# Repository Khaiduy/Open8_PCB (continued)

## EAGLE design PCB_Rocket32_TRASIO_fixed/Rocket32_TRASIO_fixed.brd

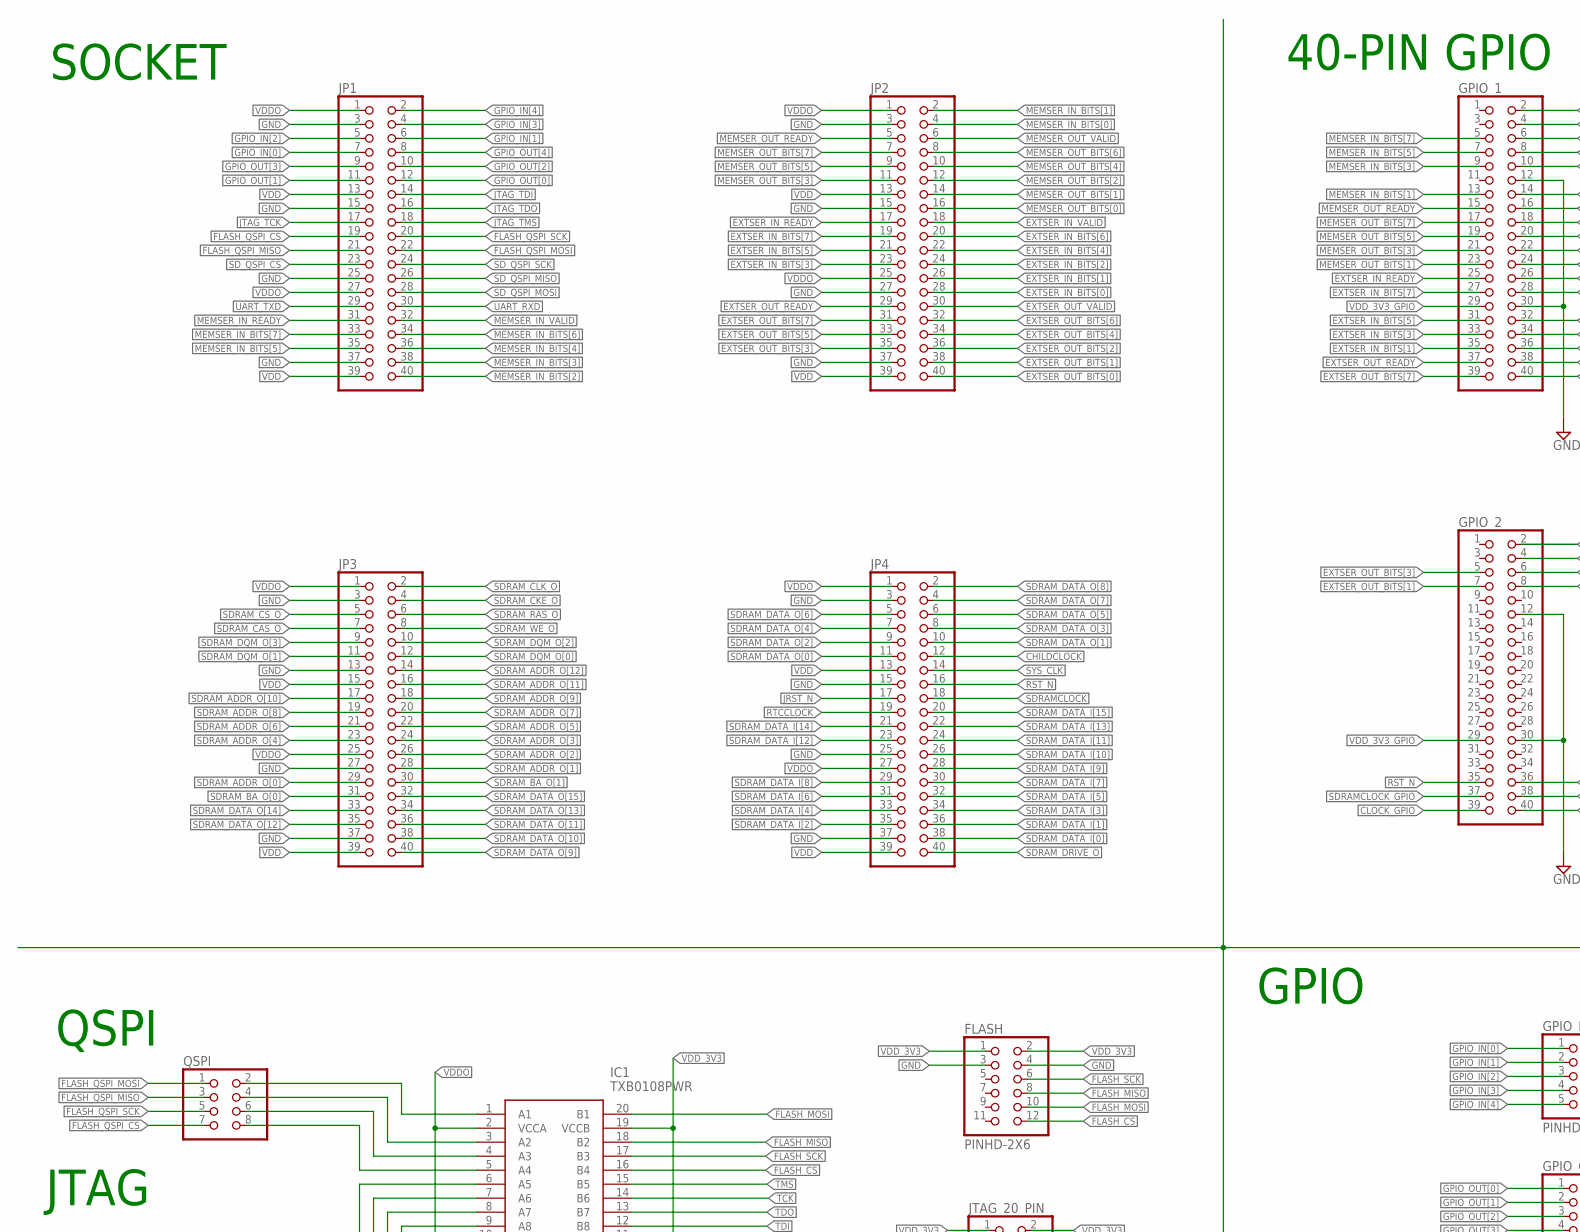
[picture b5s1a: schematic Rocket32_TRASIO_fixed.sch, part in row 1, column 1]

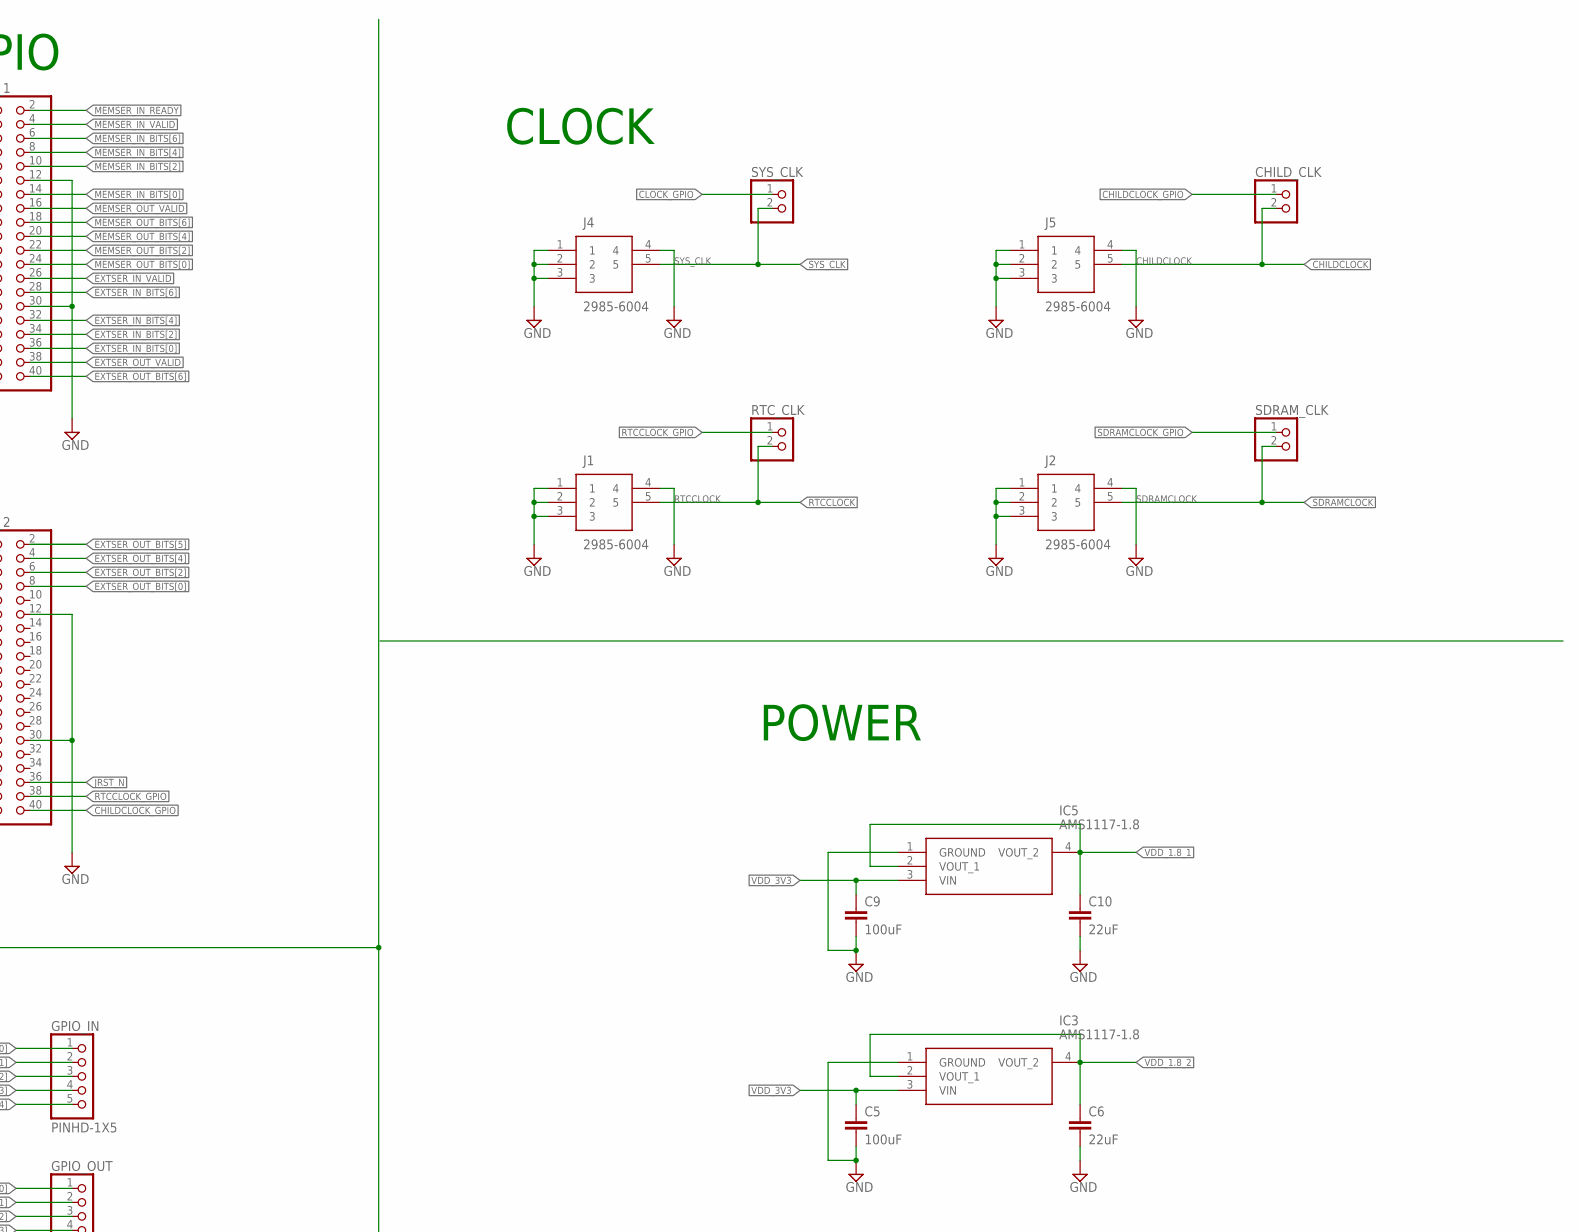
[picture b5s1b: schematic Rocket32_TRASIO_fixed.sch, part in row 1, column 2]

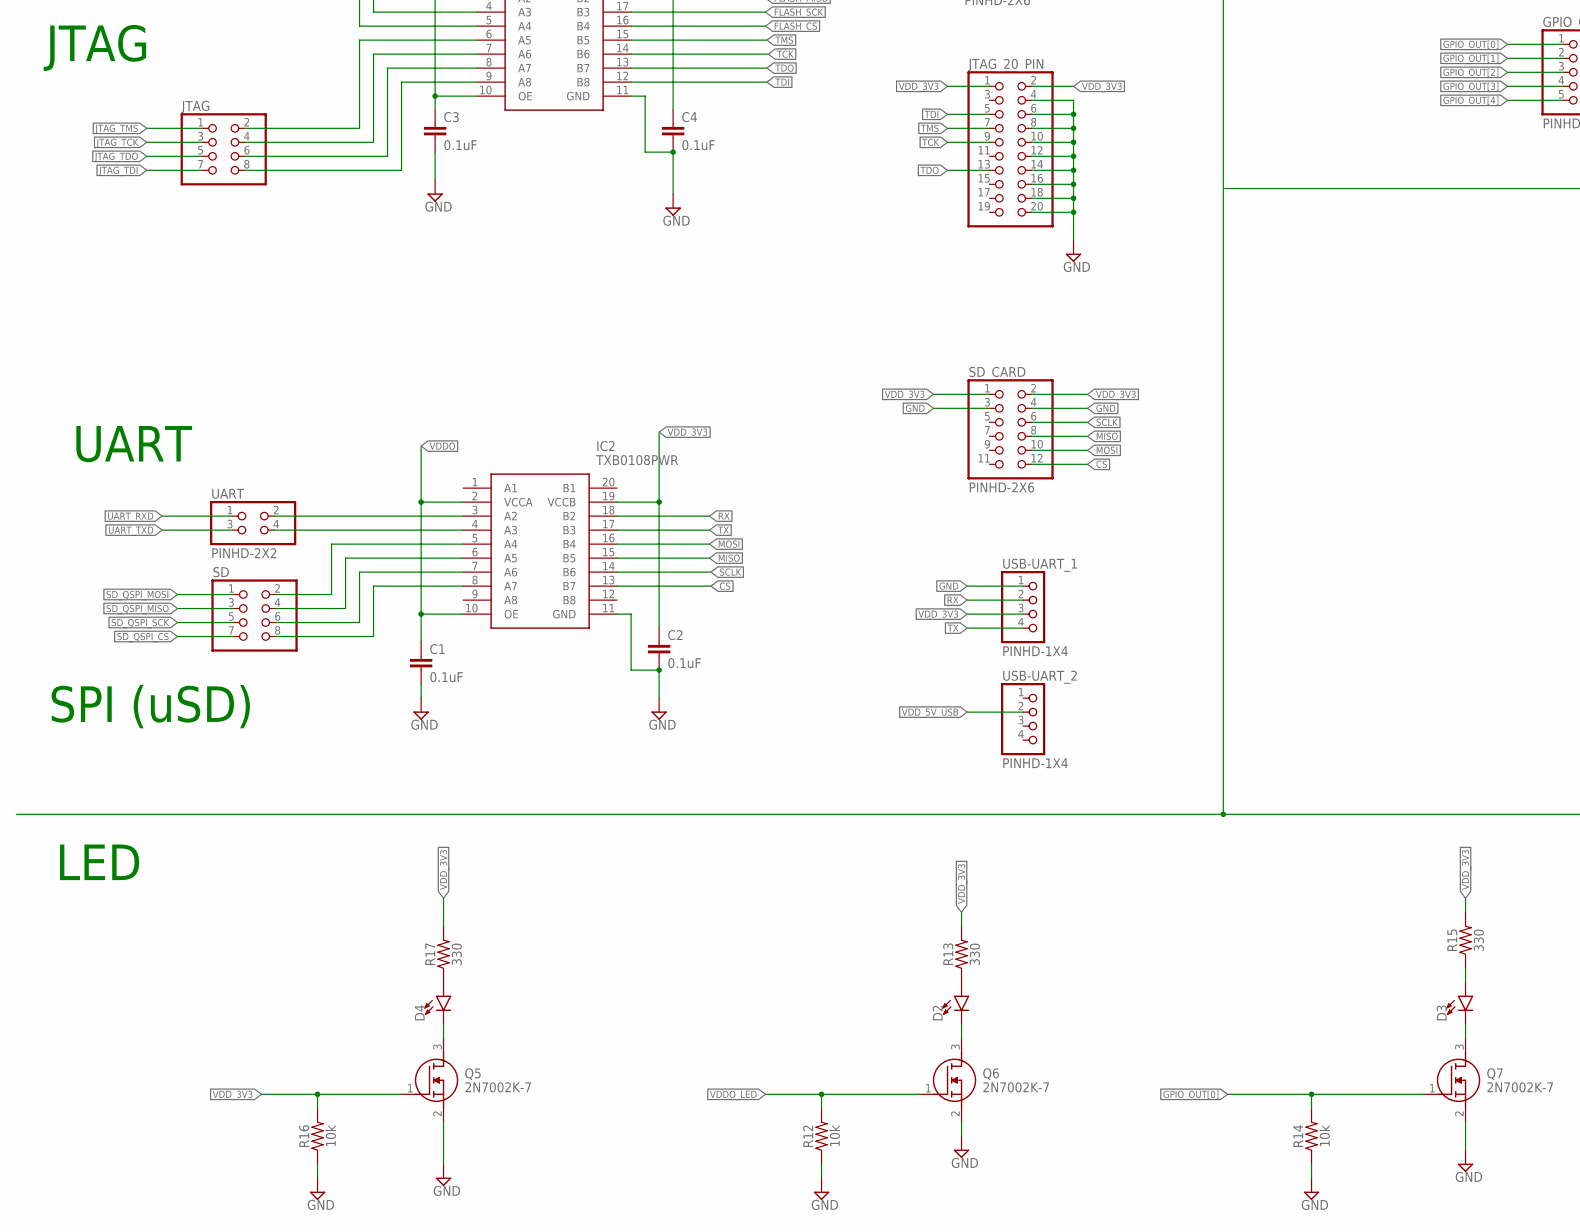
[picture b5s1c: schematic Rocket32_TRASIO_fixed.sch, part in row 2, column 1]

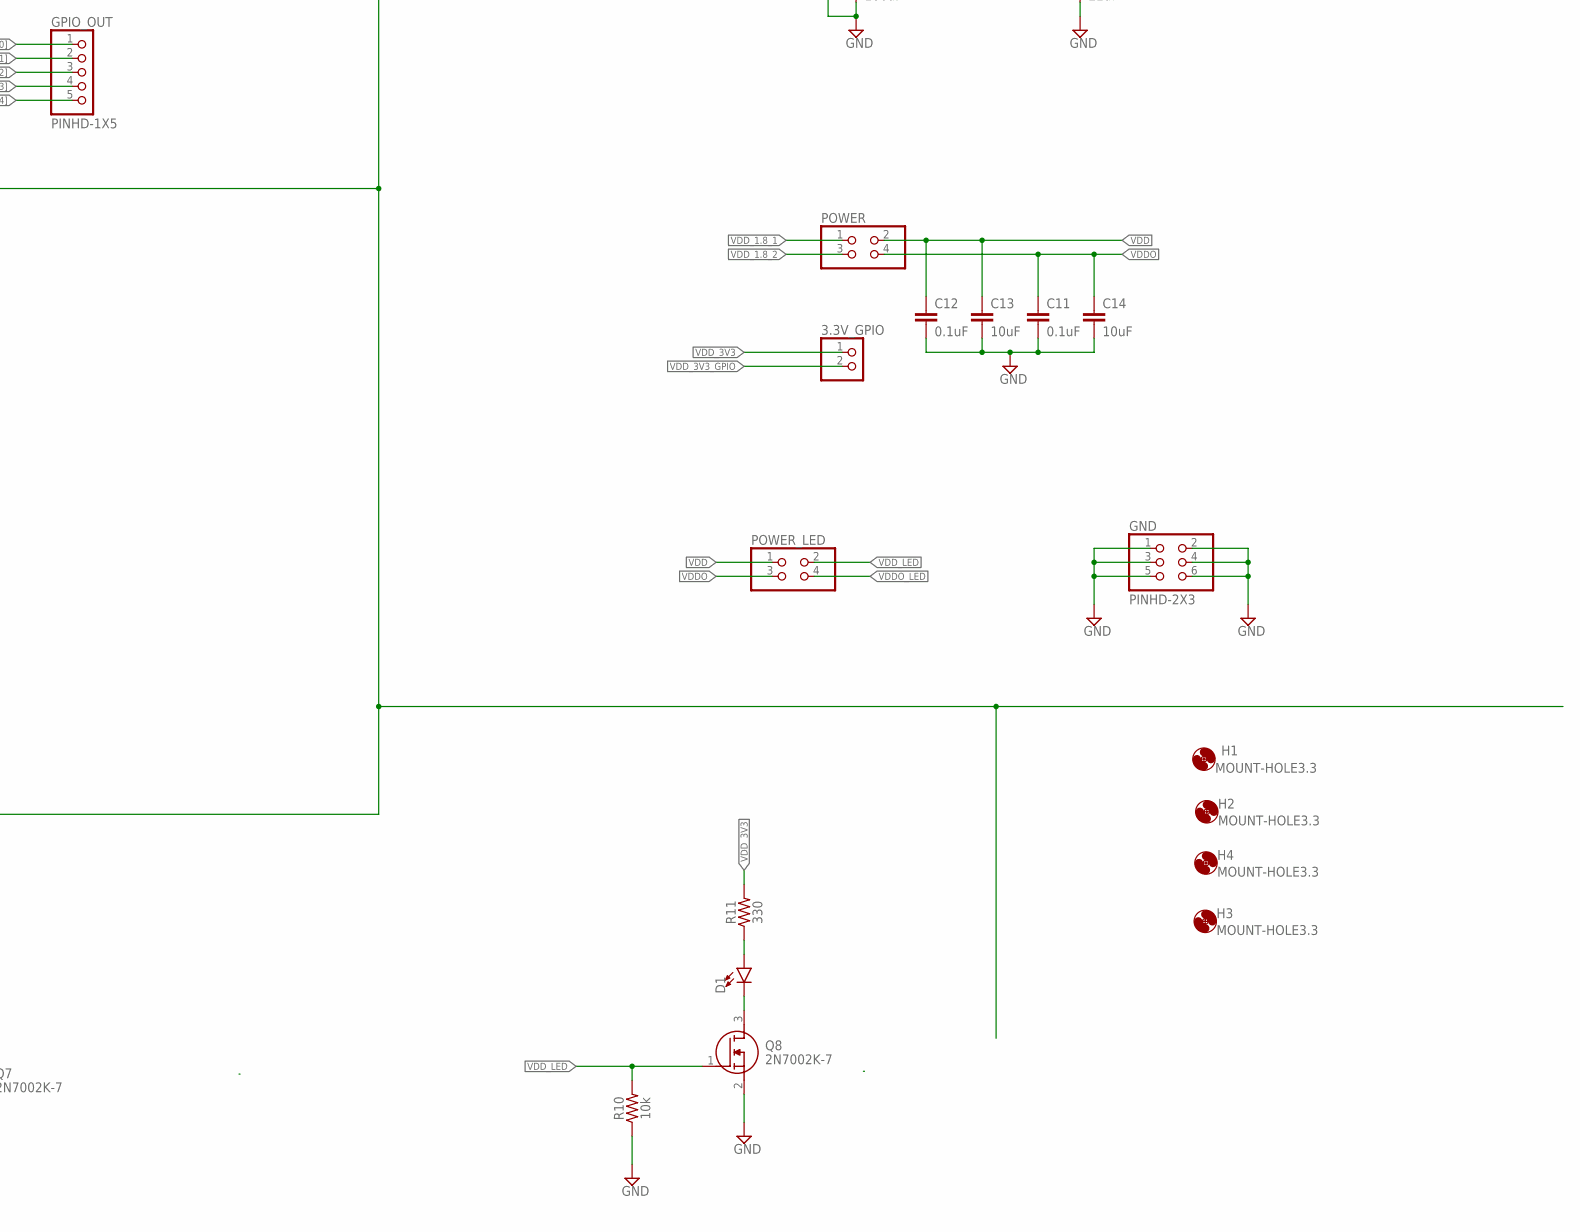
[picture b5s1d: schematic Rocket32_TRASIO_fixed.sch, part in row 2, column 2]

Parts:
3.3V_GPIO: PINHD-1X2; 1X02
C1, C2, C3, C4, C11, C12: 0.1uF; 1206
C5, C9: 100uF; 1206
C6, C10: 22uF; 1206
C13, C14: 10uF; 1206
CHILD_CLK: PINHD-1X2; 1X02
D1, D2, D3, D4: LED1206; LED-1206
FLASH: PINHD-2X6; 2X06
GND: PINHD-2X3; 2X03
GPIO_1, GPIO_2: PINHD-2X20; 2X20
GPIO_IN: PINHD-1X5; 1X05
GPIO_OUT: PINHD-1X5; 1X05
H1, H2, H3, H4: MOUNT-HOLE3.3; 3,3
IC1, IC2: TXB0108PWR; SOP65P640X120-20N
IC3, IC5: AMS1117-1.8; SOT229P700X180-4N
J1, J2, J4, J5: 2985-6004; 29856004
JP1, JP2, JP3, JP4: PINHD-2X20; 2X20
JTAG: PINHD-2X4; 2X04
JTAG_20_PIN: PINHD-2X10; 2X10
POWER: PINHD-2X2; 2X02
POWER_LED: PINHD-2X2; 2X02
Q5, Q6, Q7, Q8: 2N7002K-7; SOT96P240X100-3N
QSPI: PINHD-2X4; 2X04
R10, R12, R14, R16: 10k; 1206
R11, R13, R15, R17: 330; 1206
RTC_CLK: PINHD-1X2; 1X02
SD: PINHD-2X4; 2X04
SDRAM_CLK: PINHD-1X2; 1X02
SD_CARD: PINHD-2X6; 2X06
SYS_CLK: PINHD-1X2; 1X02
UART: PINHD-2X2; 2X02
USB-UART_1, USB-UART_2: PINHD-1X4; 1X04

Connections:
CHILDCLOCK: CHILD_CLK.2, J5.5, JP4.12
CHILDCLOCK_GPIO: CHILD_CLK.1, GPIO_2.40
CLOCK_GPIO: GPIO_2.39, SYS_CLK.1
CS: IC2.13 (B7), SD_CARD.12
EXTSER_IN_BITS[0]: GPIO_1.36, JP2.28
EXTSER_IN_BITS[1]: GPIO_1.35, JP2.26
EXTSER_IN_BITS[2]: GPIO_1.34, JP2.24
EXTSER_IN_BITS[3]: GPIO_1.33, JP2.23
EXTSER_IN_BITS[4]: GPIO_1.32, JP2.22
EXTSER_IN_BITS[5]: GPIO_1.31, JP2.21
EXTSER_IN_BITS[6]: GPIO_1.28, JP2.20
EXTSER_IN_BITS[7]: GPIO_1.27, JP2.19
EXTSER_IN_READY: GPIO_1.25, JP2.17
EXTSER_IN_VALID: GPIO_1.26, JP2.18
EXTSER_OUT_BITS[0]: GPIO_2.8, JP2.40
EXTSER_OUT_BITS[1]: GPIO_2.7, JP2.38
EXTSER_OUT_BITS[2]: GPIO_2.6, JP2.36
EXTSER_OUT_BITS[3]: GPIO_2.5, JP2.35
EXTSER_OUT_BITS[4]: GPIO_2.4, JP2.34
EXTSER_OUT_BITS[5]: GPIO_2.2, JP2.33
EXTSER_OUT_BITS[6]: GPIO_1.40, JP2.32
EXTSER_OUT_BITS[7]: GPIO_1.39, JP2.31
EXTSER_OUT_READY: GPIO_1.37, JP2.29
EXTSER_OUT_VALID: GPIO_1.38, JP2.30
FLASH_CS: FLASH.12, IC1.16 (B4)
FLASH_MISO: FLASH.8, IC1.18 (B2)
FLASH_MOSI: FLASH.10, IC1.20 (B1)
FLASH_QSPI_CS: JP1.19, QSPI.7
FLASH_QSPI_MISO: JP1.21, QSPI.3
FLASH_QSPI_MOSI: JP1.22, QSPI.1
FLASH_QSPI_SCK: JP1.20, QSPI.5
FLASH_SCK: FLASH.6, IC1.17 (B3)
GND: C1.2, C2.2, C3.2, C4.2, C5.2, C6.2, C9.2, C10.2, C11.2, C12.2, C13.2, C14.2, FLASH.3, FLASH.4, GND.1, GND.2, GND.3, GND.4, GND.5, GND.6, GPIO_1.12, GPIO_1.30, GPIO_2.12, GPIO_2.30, IC1.11 (GND), IC2.11 (GND), IC3.1 (GROUND), IC5.1 (GROUND), J1.1, J1.2, J1.3, J1.4, J2.1, J2.2, J2.3, J2.4, J4.1, J4.2, J4.3, J4.4, J5.1, J5.2, J5.3, J5.4, JP1.3, JP1.15, JP1.25, JP1.37, JP2.3, JP2.15, JP2.27, JP2.37, JP3.3, JP3.13, JP3.27, JP3.37, JP4.3, JP4.15, JP4.25, JP4.37, JTAG_20_PIN.4, JTAG_20_PIN.6, JTAG_20_PIN.8, JTAG_20_PIN.10, JTAG_20_PIN.12, JTAG_20_PIN.14, JTAG_20_PIN.16, JTAG_20_PIN.18, JTAG_20_PIN.20, Q5.2 (S), Q6.2 (S), Q7.2 (S), Q8.2 (S), R10.1, R12.1, R14.1, R16.1, SD_CARD.3, SD_CARD.4, USB-UART_1.1
GPIO_IN[0]: GPIO_IN.1, JP1.7
GPIO_IN[1]: GPIO_IN.2, JP1.6
GPIO_IN[2]: GPIO_IN.3, JP1.5
GPIO_IN[3]: GPIO_IN.4, JP1.4
GPIO_IN[4]: GPIO_IN.5, JP1.2
GPIO_OUT[0]: GPIO_OUT.1, JP1.12, Q7.1 (G), R14.2
GPIO_OUT[1]: GPIO_OUT.2, JP1.11
GPIO_OUT[2]: GPIO_OUT.3, JP1.10
GPIO_OUT[3]: GPIO_OUT.4, JP1.9
GPIO_OUT[4]: GPIO_OUT.5, JP1.8
JRST_N: GPIO_2.36, JP4.17
JTAG_TCK: JP1.17, JTAG.3
JTAG_TDI: JP1.14, JTAG.7
JTAG_TDO: JP1.16, JTAG.5
JTAG_TMS: JP1.18, JTAG.1
MEMSER_IN_BITS[0]: GPIO_1.14, JP2.4
MEMSER_IN_BITS[1]: GPIO_1.13, JP2.2
MEMSER_IN_BITS[2]: GPIO_1.10, JP1.40
MEMSER_IN_BITS[3]: GPIO_1.9, JP1.38
MEMSER_IN_BITS[4]: GPIO_1.8, JP1.36
MEMSER_IN_BITS[5]: GPIO_1.7, JP1.35
MEMSER_IN_BITS[6]: GPIO_1.6, JP1.34
MEMSER_IN_BITS[7]: GPIO_1.5, JP1.33
MEMSER_IN_READY: GPIO_1.2, JP1.31
MEMSER_IN_VALID: GPIO_1.4, JP1.32
MEMSER_OUT_BITS[0]: GPIO_1.24, JP2.16
MEMSER_OUT_BITS[1]: GPIO_1.23, JP2.14
MEMSER_OUT_BITS[2]: GPIO_1.22, JP2.12
MEMSER_OUT_BITS[3]: GPIO_1.21, JP2.11
MEMSER_OUT_BITS[4]: GPIO_1.20, JP2.10
MEMSER_OUT_BITS[5]: GPIO_1.19, JP2.9
MEMSER_OUT_BITS[6]: GPIO_1.18, JP2.8
MEMSER_OUT_BITS[7]: GPIO_1.17, JP2.7
MEMSER_OUT_READY: GPIO_1.15, JP2.5
MEMSER_OUT_VALID: GPIO_1.16, JP2.6
MISO: IC2.15 (B5), SD_CARD.8
MOSI: IC2.16 (B4), SD_CARD.10
unnamed: IC1.1 (A1), QSPI.2
unnamed: IC1.3 (A2), QSPI.4
unnamed: IC1.4 (A3), QSPI.6
unnamed: IC1.5 (A4), QSPI.8
unnamed: IC2.3 (A2), UART.2
unnamed: IC2.4 (A3), UART.4
unnamed: IC1.9 (A8), JTAG.8
unnamed: IC1.8 (A7), JTAG.6
unnamed: IC1.7 (A6), JTAG.4
unnamed: IC1.6 (A5), JTAG.2
unnamed: IC2.5 (A4), SD.2
unnamed: IC2.6 (A5), SD.4
unnamed: IC2.7 (A6), SD.6
unnamed: IC2.8 (A7), SD.8
unnamed: D4.C, Q5.3 (D)
unnamed: D2.C, Q6.3 (D)
unnamed: D3.C, Q7.3 (D)
unnamed: D1.C, Q8.3 (D)
unnamed: D1.A, R11.1
unnamed: D2.A, R13.1
unnamed: D3.A, R15.1
unnamed: D4.A, R17.1
RST_N: GPIO_2.35, JP4.16
RTCCLOCK: J1.5, JP4.19, RTC_CLK.2
RTCCLOCK_GPIO: GPIO_2.38, RTC_CLK.1
RX: IC2.18 (B2), USB-UART_1.2
SCLK: IC2.14 (B6), SD_CARD.6
SDRAMCLOCK: J2.5, JP4.18, SDRAM_CLK.2
SDRAMCLOCK_GPIO: GPIO_2.37, SDRAM_CLK.1
SDRAM_ADDR_O[0]: JP3.29
SDRAM_ADDR_O[1]: JP3.28
SDRAM_ADDR_O[2]: JP3.26
SDRAM_ADDR_O[3]: JP3.24
SDRAM_ADDR_O[4]: JP3.23
SDRAM_ADDR_O[5]: JP3.22
SDRAM_ADDR_O[6]: JP3.21
SDRAM_ADDR_O[7]: JP3.20
SDRAM_ADDR_O[8]: JP3.19
SDRAM_ADDR_O[9]: JP3.18
SDRAM_ADDR_O[10]: JP3.17
SDRAM_ADDR_O[11]: JP3.16
SDRAM_ADDR_O[12]: JP3.14
SDRAM_BA_O[0]: JP3.31
SDRAM_BA_O[1]: JP3.30
SDRAM_CAS_O: JP3.7
SDRAM_CKE_O: JP3.4
SDRAM_CLK_O: JP3.2
SDRAM_CS_O: JP3.5
SDRAM_DATA_I[0]: JP4.38
SDRAM_DATA_I[1]: JP4.36
SDRAM_DATA_I[2]: JP4.35
SDRAM_DATA_I[3]: JP4.34
SDRAM_DATA_I[4]: JP4.33
SDRAM_DATA_I[5]: JP4.32
SDRAM_DATA_I[6]: JP4.31
SDRAM_DATA_I[7]: JP4.30
SDRAM_DATA_I[8]: JP4.29
SDRAM_DATA_I[9]: JP4.28
SDRAM_DATA_I[10]: JP4.26
SDRAM_DATA_I[11]: JP4.24
SDRAM_DATA_I[12]: JP4.23
SDRAM_DATA_I[13]: JP4.22
SDRAM_DATA_I[14]: JP4.21
SDRAM_DATA_I[15]: JP4.20
SDRAM_DATA_O[0]: JP4.11
SDRAM_DATA_O[1]: JP4.10
SDRAM_DATA_O[2]: JP4.9
SDRAM_DATA_O[3]: JP4.8
SDRAM_DATA_O[4]: JP4.7
SDRAM_DATA_O[5]: JP4.6
SDRAM_DATA_O[6]: JP4.5
SDRAM_DATA_O[7]: JP4.4
SDRAM_DATA_O[8]: JP4.2
SDRAM_DATA_O[9]: JP3.40
SDRAM_DATA_O[10]: JP3.38
SDRAM_DATA_O[11]: JP3.36
SDRAM_DATA_O[12]: JP3.35
SDRAM_DATA_O[13]: JP3.34
SDRAM_DATA_O[14]: JP3.33
SDRAM_DATA_O[15]: JP3.32
SDRAM_DQM_O[0]: JP3.12
SDRAM_DQM_O[1]: JP3.11
SDRAM_DQM_O[2]: JP3.10
SDRAM_DQM_O[3]: JP3.9
SDRAM_DRIVE_O: JP4.40
SDRAM_RAS_O: JP3.6
SDRAM_WE_O: JP3.8
SD_QSPI_CS: JP1.23, SD.7
SD_QSPI_MISO: JP1.26, SD.3
SD_QSPI_MOSI: JP1.28, SD.1
SD_QSPI_SCK: JP1.24, SD.5
SYS_CLK: J4.5, JP4.14, SYS_CLK.2
TCK: IC1.14 (B6), JTAG_20_PIN.9
TDI: IC1.12 (B8), JTAG_20_PIN.5
TDO: IC1.13 (B7), JTAG_20_PIN.13
TMS: IC1.15 (B5), JTAG_20_PIN.7
TX: IC2.17 (B3), USB-UART_1.4
UART_RXD: JP1.30, UART.1
UART_TXD: JP1.29, UART.3
VDD: C12.1, C13.1, JP1.13, JP1.39, JP2.13, JP2.39, JP3.15, JP3.39, JP4.13, JP4.39, POWER.2, POWER_LED.1
VDDO: C1.1, C3.1, C11.1, C14.1, IC1.2 (VCCA), IC1.10 (OE), IC2.2 (VCCA), IC2.10 (OE), JP1.1, JP1.27, JP2.1, JP2.25, JP3.1, JP3.25, JP4.1, JP4.27, POWER.4, POWER_LED.3
VDDO_LED: POWER_LED.4, Q6.1 (G), R12.2
VDD_1.8_1: C10.1, IC5.2 (VOUT_1), IC5.4 (VOUT_2), POWER.1
VDD_1.8_2: C6.1, IC3.2 (VOUT_1), IC3.4 (VOUT_2), POWER.3
VDD_3V3: 3.3V_GPIO.1, C2.1, C4.1, C5.1, C9.1, FLASH.1, FLASH.2, IC1.19 (VCCB), IC2.19 (VCCB), IC3.3 (VIN), IC5.3 (VIN), JTAG_20_PIN.1, JTAG_20_PIN.2, Q5.1 (G), R11.2, R13.2, R15.2, R16.2, R17.2, SD_CARD.1, SD_CARD.2, USB-UART_1.3
VDD_3V3_GPIO: 3.3V_GPIO.2, GPIO_1.29, GPIO_2.29
VDD_5V_USB: USB-UART_2.2
VDD_LED: POWER_LED.2, Q8.1 (G), R10.2

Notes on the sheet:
QSPI
SPI (uSD)
JTAG
UART
POWER
CLOCK
LED
GPIO
SOCKET
40-PIN GPIO

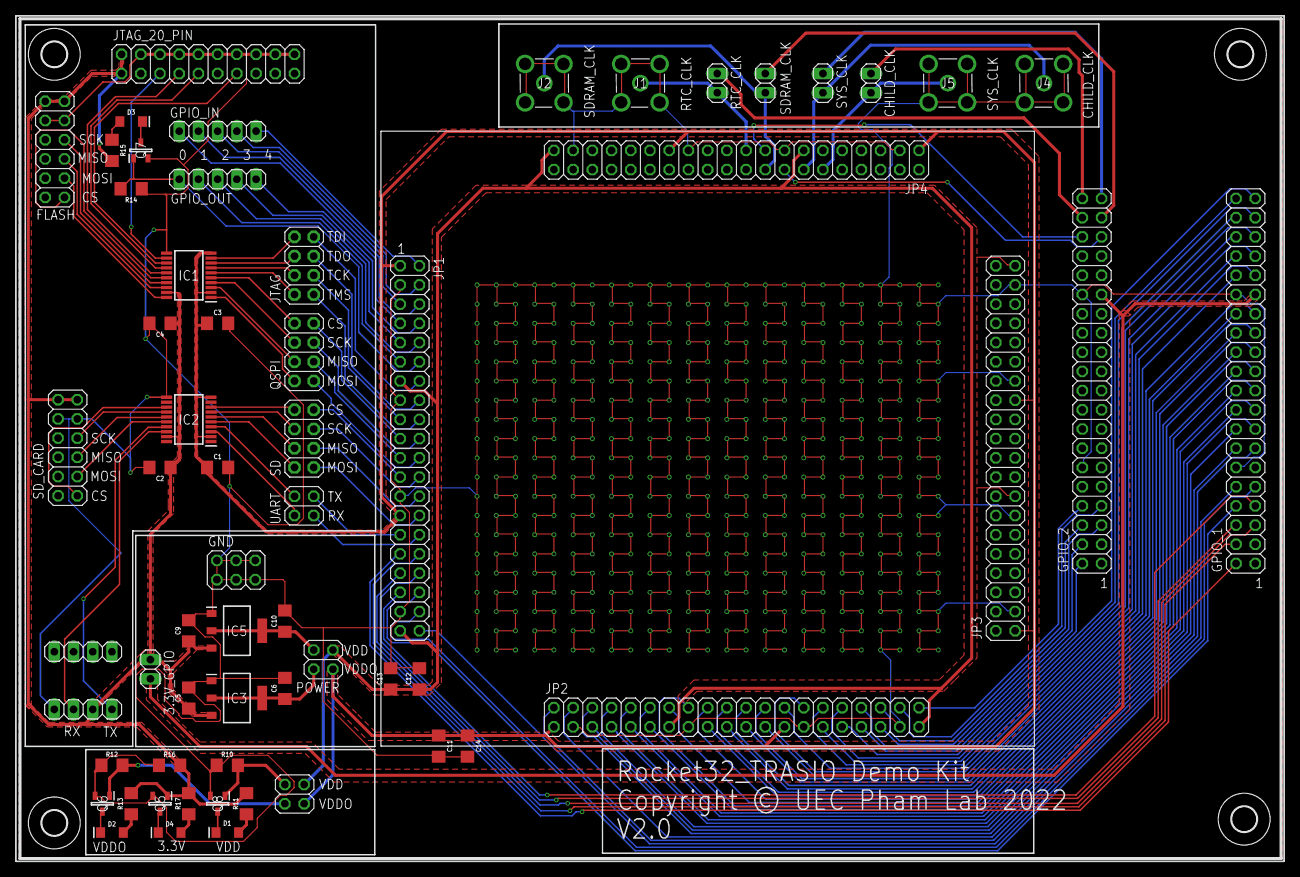
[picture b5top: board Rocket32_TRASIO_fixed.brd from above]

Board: 2 copper layers, 167.6 x 111.8 mm, 65 parts (1 on the bottom side), 119 nets.
